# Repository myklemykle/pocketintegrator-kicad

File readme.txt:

LICENSE STATEMENT:

The hardware design in this repo is released under the GNU GPL Version 3.0 (and later).
The documentation is released under the Creative Commons Attribution Share Alike 4.0 International license.
These liceneses, and other licenses for third-party symbols, footprints and models included in this repo,
can be found under /library/licenses .

DESCRIPTION:

Pocket Integrator v11 (PI) is an add-on board for Pocket Operator (PO) series of 
handheld drum/rhythm instruments made by Teenage Engineering SA.  It hosts a
Raspberry Pi RP2040 mcu, a LSM6DSO-series accelerometer from STMicro, a 1.8v
QSPI-compatible flash memory chip in 8-pin SOIC format (such as a Winbond W25Q128JW),
a few power supply/buffer ICs, four tactile switches, and misc SMD passives and connectors.

This PI board fits snugly to the back of any model of PO, but must be held in place
with two rubber bands.  I recommend a pair of neoprene O-rings, size 027, 70 durometer.

Four GPIO pin connections are made through anti-aliasing audio-pass filters to 
a pair of 3.5mm TRS connectors. These can be used either for PWM audio output
or analog audio input.

PI can draw power either from the PO batteries when attached to the PO, 
or from the USB-C port when connected to a suitable USB-C host.
When attached to USB power, PI can supply current back to the attached
PO, allowing it to run without batteries installed.

Pin connections are made from RP2040 GPIO pins to the SWD pins of the PO, 
allowing PI to be used as a debugger and reprogrammer for POs.  
The PO Play LED is also connected to GPIO, so the PI can know if the PO is playing.  

All these pin connections are made between a pogo-pin block on the PI 
and 12 programming/debug pads on the back of every PO. 
The 6x2 grid of pogo pin connectors should have these measurements:

	.100" (2,540mm) Pitch
	.055" (1,397mm) Stroke
	.236" (5,994mm) Initial Height

Compatible 6x2 pogo pin blocks are available from Mill-Max and Preci-Dip. 
Other pogo pin options may exist by combining smaller block arrangements.
(If necessary, a 5x2 block of pins can be used, 
as the sixth column consists only of redundant ground connections.)

FILES:

integrator.*, integrator-cache.*: 
	KiCad project files.
	NOTE: Pocket Integrator was designed with KiCad version 5, 
	and has not been tested with later versions. 

gerber/: 
	exported gerber files for fabrication.

library/: 
	models, symbols and footprints used by KiCad.

pins.h: 
	Documenation of RP2040 pin connections to the rest of the board.

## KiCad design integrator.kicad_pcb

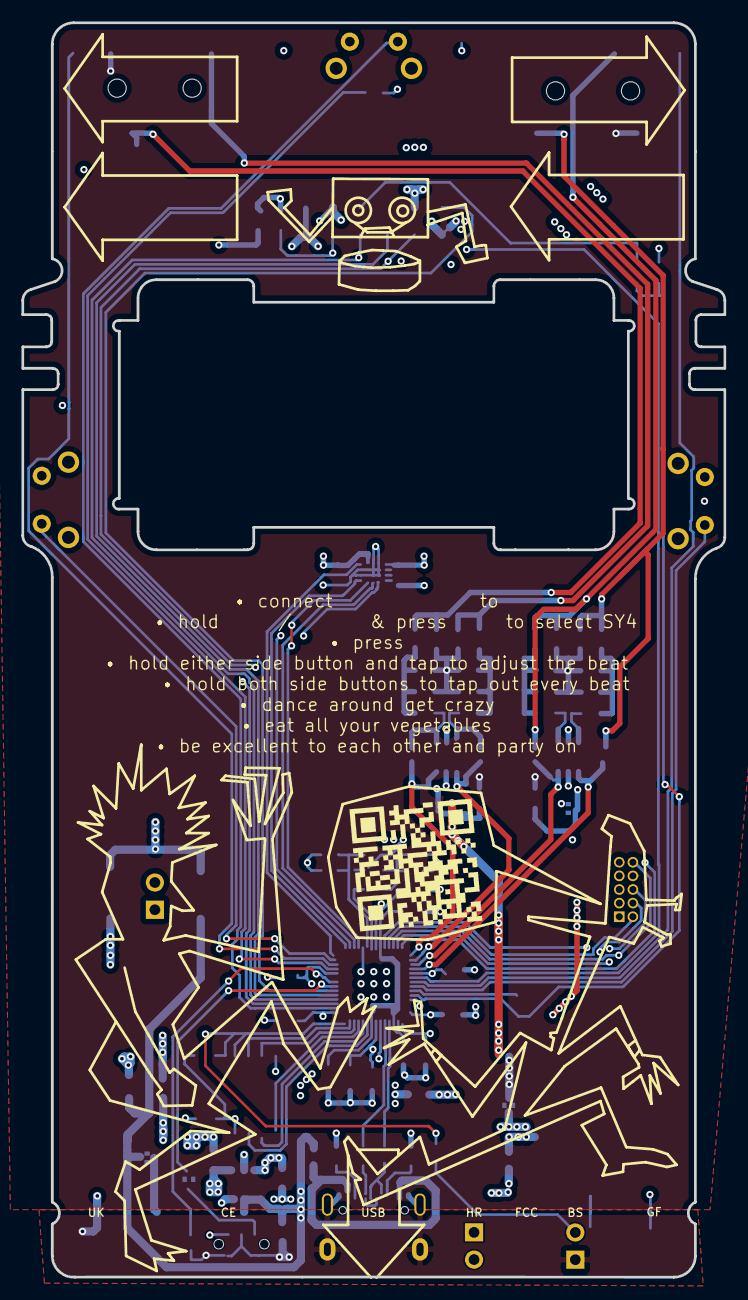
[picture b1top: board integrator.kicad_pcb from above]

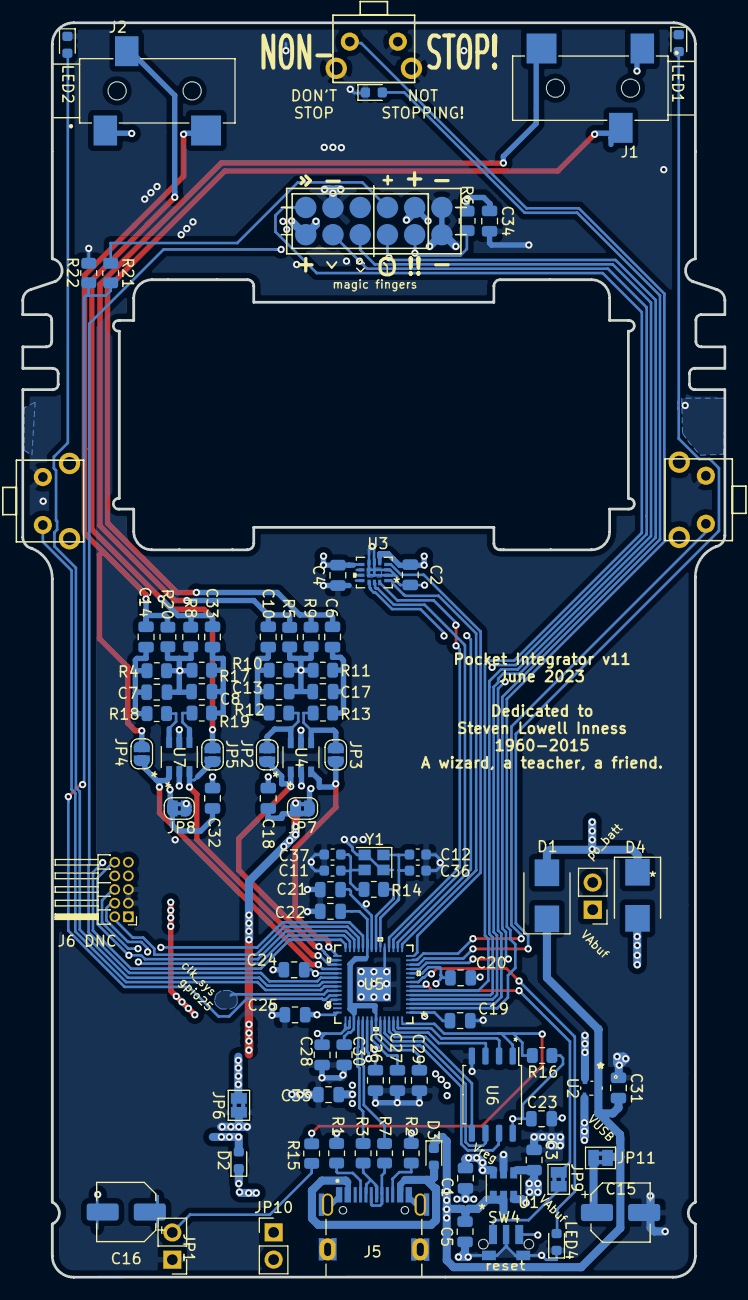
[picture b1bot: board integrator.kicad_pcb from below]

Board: 4 copper layers, 65.5 x 117.0 mm, 95 parts (95 on the bottom side), 72 nets.

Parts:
C1, C3, C5: 1uf ceramic; C_0805_2012Metric
C2, C4, C18, C19, C20, C21, C22, C23, C24, C25, C26, C27, C29, C32, C34, C35: 0.1uf; C_0805_2012Metric
C6, C10, C14, C33: 47uf; C_0805_2012Metric
C7, C8, C13, C17: 0.1uf 5%; C_0805_2012Metric
C11, C12: 6pf; C_0603_1608Metric
C15, C16: 100uf; CP_Elec_5x4.4
C28, C30: 1uf; C_0805_2012Metric
C31: 0.1uf ceramic; C_0805_2012Metric
C36, C37: TBD/DNC; C_0603_1608Metric
D1: <100mv drop; D_SMB
D2: shottky; D_0603_1608Metric
D3: 450mv drop; D_0603_1608Metric
D4: 200mv drop; D_SMB
J1, J2: SJ-3523-SMT; CUI_SJ-3523-SMT-TR
J5: USB4105-GF-A; HRO_TYPE-C-31-M-12-Paste-Lugs
J6 DNC: Conn_ARM_JTAG_SWD_10; PinHeader_2x05_P1.27mm_Horizontal
J7: test point; PinHeader_1x02_P2.54mm_Vertical
JP1: Jumper_NO_Small; PinHeader_1x02_P2.54mm_Vertical
JP2, JP3, JP4, JP5: Jumper_NO_Small; SolderJumper-2_P1.3mm_Open_RoundedPad1.0x1.5mm
JP6, JP9, JP11: Jumper; SolderJumper-2_P1.3mm_Bridged2Bar_Pad1.0x1.5mm
JP7, JP8: Jumper_NC_Small; SolderJumper-2_P1.3mm_Bridged2Bar_RoundedPad1.0x1.5mm
JP10: Jumper; PinHeader_1x02_P2.54mm_Vertical
LED1, LED2, LED3, LED4: CSL1901VW1; LED_0603_1608Metric
POGO1: PO pogos; 813-22-012-30-004101-millmax-pogopins-2x6
R1, R2, R6: 5.1k; R_0805_2012Metric
R3, R7: 27 5%; R_0805_2012Metric
R4, R10, R11, R17: 100 1%; R_0805_2012Metric
R5, R8, R9, R20: 1.8K 1%; R_0805_2012Metric
R12, R13, R18, R19: 220 1%; R_0805_2012Metric
R14, R15: 1k 5%; R_0805_2012Metric
R16: 10k; R_0805_2012Metric
R21: 100k; R_0805_2012Metric
R22: 220k; R_0805_2012Metric
SW1, SW2, SW3: EVQP40B3M; TL1105VF100Q
SW4: 436333033816
U1: XC6415; SOT-23-6
U2: XC6501D331NR-G
U3: LSM6DSO32XTR
U4, U7: NL27WZ16DTT1G
U5: RP2040
U6: IS25WP128F-JBLE; SOIC-8_5.23x5.23mm_P1.27mm
Y1: Crystal; Crystal_SMD_2520-4Pin_2.5x2.0mm

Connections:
/PWM_L1: JP2.1, R12.2, U4.6
/PWM_L2: R18.2, U7.6
/PWM_LL1: C10.2, C13.1, R10.2, R12.1
/PWM_LL2: C7.1, C14.2, R4.2, R18.1
/PWM_R1: JP3.1, R13.2, U4.4
/PWM_R2: R19.2, U7.4
/PWM_RR1: C6.2, C17.1, R11.2, R13.1
/PWM_RR2: C8.1, C33.2, R17.2, R19.1
/po_batt: C34.1, D1.2, D4.1, J7.2, POGO1.4, POGO1.11, R6.1
/xin: C12.2, C36.2, U5.20, Y1.1
/xout: R14.1, U5.21
AGnd: C7.2, C8.2, C13.2, C17.2, C18.2, C32.2, J1.1, J2.1, JP6.1, R4.1, R5.1, R8.1, R9.1, R10.1, R11.1, R17.1, R20.1
Aref_enable: U1.3, U5.39
Earth: C1.1, C2.2, C3.2, C4.2, C5.1, C11.2, C12.1, C15.2, C19.2, C20.2, C21.2, C22.2, C23.2, C24.2, C25.2, C26.2, C27.2, C28.1, C29.2, C30.1, C31.2, C34.2, C35.2, C36.1, C37.2, J5.S1, J5.S2, J5.S3, J5.S4, J6 DNC.3, J6 DNC.5, JP1.1, JP6.2, LED1.1, LED2.1, LED3.1, LED4.1, POGO1.1, POGO1.2, POGO1.10, R1.2, R2.1, R22.1, SW1.2, SW1.3, SW1.4, SW2.1, SW2.3, SW2.4, SW3.1, SW3.3, SW3.4, SW4.2, SW4.mp1, SW4.mp2, U1.5, U2.2, U3.2, U3.3, U3.6, U3.7, U4.2, U5.19, U5.57, U6.4, U7.2
unnamed: C11.1, C37.1, R14.2, Y1.3
unnamed: C15.1, JP11.2
unnamed: C18.1, JP7.1, U4.5
unnamed: C32.1, JP8.2, U7.5
unnamed: D2.2, J6 DNC.7
unnamed: J5.A5, R1.1
unnamed: J5.A6, J5.B6, R7.1
unnamed: J5.A7, J5.B7, R3.2
unnamed: J5.B5, R2.2
unnamed: JP1.2, R15.2
unnamed: JP9.2, SW4.1
unnamed: JP10.2, SW4.3
unnamed: POGO1.6, R21.2
unnamed: R15.1, R16.1, U5.56, U6.1
unnamed: U5.51, U6.7
unnamed: U5.52, U6.6
unnamed: U5.53, U6.5
unnamed: U5.54, U6.3
unnamed: U5.55, U6.2
VAbuf: C3.1, D4.2, J7.1, JP7.2, JP8.1, U1.4
VInt: C22.1, C29.1, C30.2, U5.23, U5.45, U5.50
VRaw: C5.2, C31.1, D1.1, D2.1, D3.1, JP11.1, U1.1, U1.2, U2.1, U2.4
VReg: C1.2, C2.1, C4.1, C19.1, C20.1, C21.1, C23.1, C24.1, C25.1, C26.1, C27.1, C28.2, R16.2, U1.6, U3.5, U3.8, U5.1, U5.10, U5.22, U5.33, U5.42, U5.43, U5.44, U5.49, U6.8
VUSB: C35.1, U2.3, U5.48
imu_int: U3.4, U5.14
led1: LED1.2, U5.12
led2: LED2.2, U5.35
led3: LED3.2, U5.11
led4: LED4.2, U5.8
pi_reset: J6 DNC.10, JP10.1, U5.26
pi_swclk: J6 DNC.4, U5.24
pi_swdio: J6 DNC.2, U5.25
pi_swo: J6 DNC.6, U5.27
pi_txin: J6 DNC.8, U5.28
po_play: POGO1.12, U5.6
po_reset: POGO1.3, R6.2, U5.34
po_swclk: POGO1.5, U5.4
po_swdio: POGO1.7, U5.5
po_swo: POGO1.9, U5.3
po_wake: R21.1, R22.2, U5.38
ring1: JP3.2, U4.3, U5.29
ring1_out: C6.1, J1.3, R9.2
ring2: JP5.1, U5.31, U7.3
ring2_out: C33.1, J2.3, JP5.2, R8.2
spi_clock: U3.13, U5.17
spi_cs: U3.12, U5.16
spi_miso: U3.1, U5.15
spi_mosi: U3.14, U5.18
sw1: SW1.1, U5.13
sw2: SW2.2, U5.36
sw3: SW3.2, U5.2
sw4: JP9.1, U5.7
tip1: JP2.2, U4.1, U5.30
tip1_out: C10.1, J1.2, R5.2
tip2: JP4.1, U5.32, U7.1
tip2_out: C14.1, J2.2, JP4.2, R20.2
usb_d+: R7.2, U5.47
usb_d-: R3.1, U5.46

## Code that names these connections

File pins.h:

#ifndef __PINS_H
#define __PINS_H

// Pins:
const int button1Pin = 10;   // sw1 = gpio10
const int button2Pin = 24;   // sw2 = gpio24
const int button3Pin = 0;   // sw3/nonstop
const int button4Pin = 5;   // sw4/reset
const int led1Pin =  9;    // pwm channel 4B
const int led2Pin =  23;    // pwm channel 3B
const int led3Pin = 8; // pwm channel 4A
const int nonstopLedPin = led3Pin; 
const int led4Pin = 6;	// pwm channel 3A
const int boardLedPin = led4Pin;
const int tip1 = 19; 	// pwm channel 1B
const int tip2 = 21; 		// pwm channel 2B
const int ring1 = 18; // pwm channel 1A
const int ring2 = 20;	// pwm channel 2A
const int outPins[4] = { tip1, ring1, tip2, ring2 };
const int PO_play = 4; 		// goes high on PO play (runs to play LED)
const int PO_wake = 26;			// goes low when PO sleeps -- gpio26/adc0
const int PO_reset = 22;			
const int PO_SWCLK = 2;			// jtag/stlink pins:
const int PO_SWDIO = 3;
const int PO_SWO   = 1;
const int IMU_int = 11;
const int SPI_clock = 14;
const int SPI_cs = 13;
const int SPI_miso = 12;
const int SPI_mosi = 15;
// drive Aref_enable high to enable 2.5v audio power supply
const int Aref_enable = 27; 
// Unused pins must be tied high or low, or else the whole CMOS chip can glitch.
const int unusedPins[6] = { 7,16,17,25,28,29 };
// These are normally unused, but used in testing/debug:
// a UART for picoprobe or misc future handiness, goes to JTAG pins
const int PI_swo = 16; // UART0 TX
const int PI_txin = 17; // UART0 RX
// For testing/tuning crystal, RP2040 can send clk_sys direct to this pin:
const int PI_clk_sys = 25;

#endif // PINS_H 

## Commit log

2021-02-22 ignore
2021-03-13 saved before library tweak
2021-03-22 snapshot everything for safety
2021-03-26 snapshot with hackzone
2021-03-26 bye bye hackzone
2021-06-22 last changes of rev3
2021-07-06 evt4 schem w/o rocker switches
2021-07-06 5x2 pogo
2021-07-10 evt4 pcb layout
2021-07-11 even more final evt4
2021-07-12 evt4 submitted to oshpark
2021-08-11 moved po_wake to analog pin 14 +tweaks
2022-04-09 gerbers
2022-04-09 tighter slot, narrower kickstand
2022-04-23 be more ignorant
2022-04-23 breakout tab
2022-04-23 gerbers to jblpcb
2022-05-07 version 5 schematic complete
2022-05-09 libs & models
2022-05-09 rev5 pcb checkpoint (close)
2022-05-19 v5 sent to fab
2022-05-19 cleanup unused stuff
2022-05-19 dont submodule templates
2022-05-19 cleanup & readme
2022-09-13 tweaks/fixes to v5
2022-09-13 ignore fp-info-cache
2022-09-13 v5 gerbers as sent to pcbway
2022-09-13 major cleanup/reorg of symbols and footprints
2022-09-13 clean/reorg models, dcm files, dir-splat
2022-09-15 munged components
2022-09-15 WIP before schematic append
2022-09-16 v6 schematic complete
2022-09-19 lib/footprint tweaks/fixes for pcbnew
2022-09-19 schematic tweaks/fixes
2022-09-20 WIP routing pcb
2022-09-20 WIP mostly placed
2022-09-20 WIP before tidying/tweaking btm layer
2022-09-20 WIP all traces laid
2022-09-21 fixed dup values
2022-09-21 passed DRC
2022-09-21 added xtal model
2022-09-21 removed bridge plug
2022-09-22 completed front artwork
2022-09-22 tweaked kickstand slots
2022-09-23 corrected gerbers sent to fab
2022-10-08 tweaks & fixes
2022-10-08 ignore more
2022-10-08 slot tweaks
2022-10-10 outline on pogo pads
2022-10-10 compliance logos
2022-10-10 bugfixes on v6
2022-11-09 v7 gerbers sent to jlc
2022-11-09 adj popcorn spacing
2022-12-10 changing to ABM10-166-12.000MHZ-T3 crystal
2022-12-10 repositioned audio output stage
2023-01-03 adjusted jack positions, added back jumper
2023-01-08 widened edges to 60mm, re-added jumper
2023-01-11 fix model bug
2023-01-11 v8 schematic & pcb
2023-01-11 reorg po debug pins
2023-01-12 test points & tweaks
2023-01-12 moved logos, misc tweaks
2023-01-13 resistor tweaks
2023-01-13 v8 gerbers as sent
2023-02-08 tweaks
2023-02-21 v9 checkpoint/wip
2023-02-21 v9 schematic updates
2023-02-21 v9 checkpoint 2
2023-02-21 v9 checkpoint 3
2023-02-22 possibly finished v9
2023-02-22 sysclk testpad, jmpr cleanup
2023-02-22 hard reset jumper open
2023-02-22 update D2 comment
2023-03-31 final v9 gerbers to jlcpcb
2023-03-31 vreg to jtag pin 1
2023-03-31 sj-3523
2023-04-04 jumper & capacitor tweaks
2023-04-11 qrcode & misc tweaks
2023-04-13 v10 submission #1
2023-04-28 mod pogo1 footprint for 2x5 connector
2023-04-30 10.1 gerbers sent to CCC for quote
2023-04-30 clearer QRcode
2023-07-07 larger instructions
2023-07-07 tweak ground planes
2023-07-07 v11 sent to JLC 7/7/2023
2023-09-07 added drill/place origin, remade gerbers
2023-11-20 library cleanup
2023-11-20 dont ignore gerbers
2023-11-20 v11 symbols list
2023-11-20 updated readme & licenses
2023-11-20 pin documentation

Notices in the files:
parts and their libraries:
Copyright 2021 Accelerated Designs. All rights reserved.
Copyright 2016 Accelerated Designs. All rights reserved.
